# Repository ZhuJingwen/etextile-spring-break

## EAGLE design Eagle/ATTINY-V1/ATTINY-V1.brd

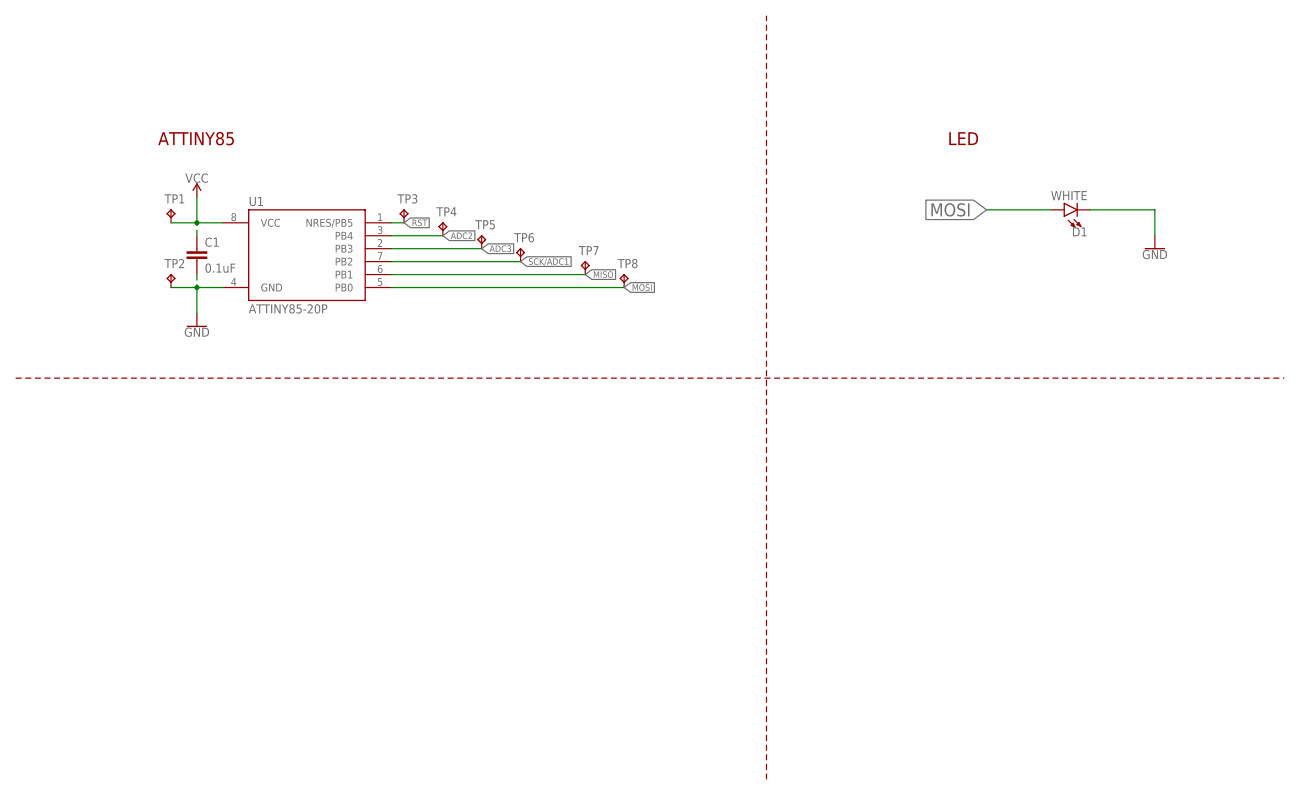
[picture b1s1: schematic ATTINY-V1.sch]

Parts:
C1: 0.1uF; CAP-PTH-SMALL-KIT
D1: WHITE; LED-1206
TP1, TP2, TP3, TP4, TP5, TP6, TP7, TP8: TPTP20R; TP20R
U1: ATTINY85-20P; PDIP08_300MIL

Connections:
ADC2: TP4.TP, U1.3 (PB4)
ADC3: TP5.TP, U1.2 (PB3)
GND: C1.2, D1.C, TP2.TP, U1.4 (GND)
MISO: TP7.TP, U1.6 (PB1)
MOSI: D1.A, TP8.TP, U1.5 (PB0)
RST: TP3.TP, U1.1 (NRES/PB5)
SCK/ADC1: TP6.TP, U1.7 (PB2)
VCC: C1.1, TP1.TP, U1.8 (VCC)

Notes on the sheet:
ATTINY85
LED

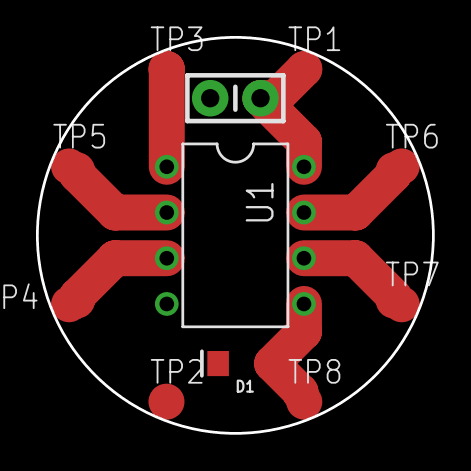
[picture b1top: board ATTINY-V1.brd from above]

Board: 2 copper layers, 22.0 x 22.0 mm, 11 parts (0 on the bottom side), 8 nets.

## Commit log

2019-04-11 init

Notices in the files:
parts and their libraries:
SparkFun-LED: Licensing: Creative Commons ShareAlike 4.0 International - https://creativecommons.org/licenses/by-sa/4.0
